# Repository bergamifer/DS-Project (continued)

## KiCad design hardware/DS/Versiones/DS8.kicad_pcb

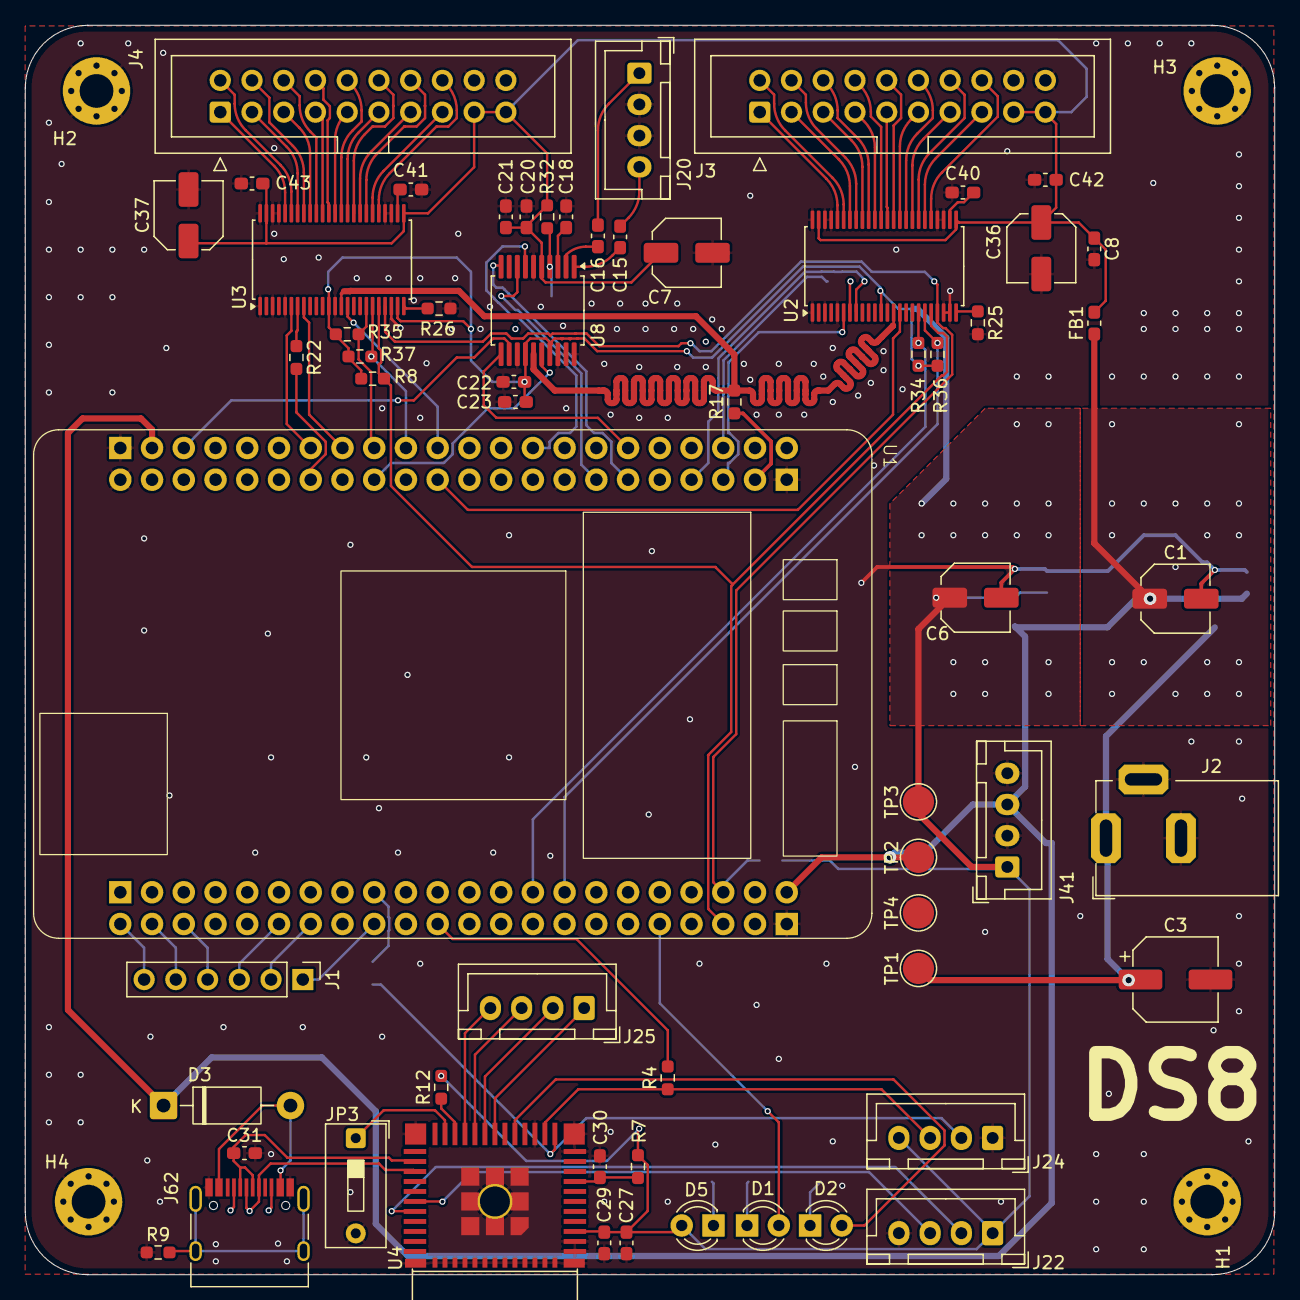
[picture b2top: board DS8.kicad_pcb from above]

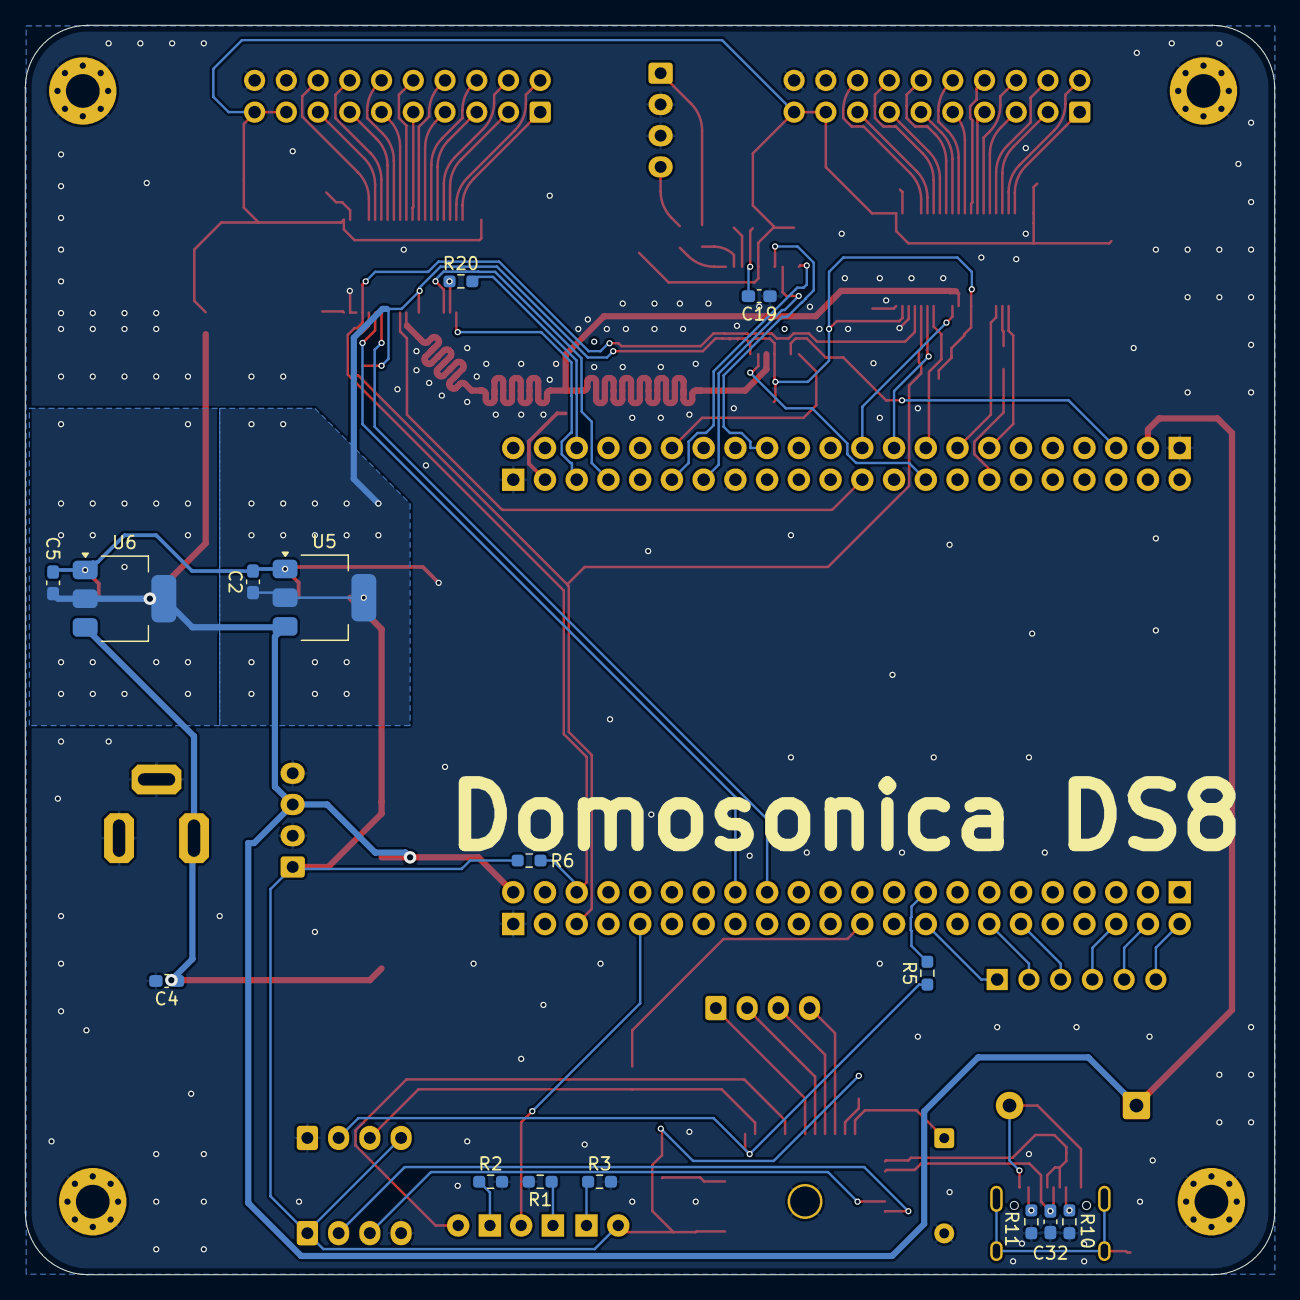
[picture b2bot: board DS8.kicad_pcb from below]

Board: 2 copper layers, 100.0 x 100.0 mm, 80 parts (15 on the bottom side), 101 nets.

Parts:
C1, C6, C7, C36, C37: 10u; C_Elec_5x5.4
C2, C4, C5, C8, C18, C19, C20, C23, C29, C30: 0.1u; C_0603_1608Metric_Pad1.08x0.95mm_HandSolder
C3: 100u; CP_Elec_6.3x5.4
C15, C16, C40, C41, C42, C43: 1u; C_0603_1608Metric_Pad1.08x0.95mm_HandSolder
C21, C22, C27: 10u; C_0603_1608Metric_Pad1.08x0.95mm_HandSolder
C31, C32: 22pF; C_0603_1608Metric_Pad1.08x0.95mm_HandSolder
D1, D2, D5: LED; LED_D3.0mm
D3: 1N5819; D_DO-41_SOD81_P10.16mm_Horizontal
FB1: FerriteBead; L_0603_1608Metric_Pad1.05x0.95mm_HandSolder
H1, H2, H3, H4: MH; MountingHole_2.7mm_Pad_Via
J1: Optional header; PinHeader_1x06_P2.54mm_Vertical
J2: 12v; BarrelJack_CUI_PJ-102AH_Horizontal
J3, J4: Conn_02x10_Odd_Even; IDC-Header_2x10_P2.54mm_Vertical
J20: Audio_IN; JST_XH_B4B-XH-A_1x04_P2.50mm_Vertical
J22: UART0_ESP32; JST_XH_B4B-XH-A_1x04_P2.50mm_Vertical
J24: UART1_ESP32; JST_XH_B4B-XH-A_1x04_P2.50mm_Vertical
J25: JTAG; JST_XH_B4B-XH-A_1x04_P2.50mm_Vertical
J41: Opt_Vout; JST_XH_B4B-XH-A_1x04_P2.50mm_Vertical
J62: USB_C_Receptacle_USB2.0_16P; USB_C_Receptacle_HRO_TYPE-C-31-M-12
JP3: BOOT_ESP32; SW_DIP_SPSTx01_Slide_9.78x4.72mm_W7.62mm_P2.54mm
R1, R3, R25, R26, R32, R34, R35, R36, R37: 1k; R_0603_1608Metric_Pad0.98x0.95mm_HandSolder
R2, R4, R5: 220; R_0603_1608Metric_Pad0.98x0.95mm_HandSolder
R6, R8, R10, R11: 5.1k; R_0603_1608Metric_Pad0.98x0.95mm_HandSolder
R7, R12: 10k; R_0603_1608Metric_Pad0.98x0.95mm_HandSolder
R9: 1M; R_0603_1608Metric_Pad0.98x0.95mm_HandSolder
R17, R20, R22: 33; R_0603_1608Metric_Pad0.98x0.95mm_HandSolder
TP1: +12; TestPoint_Pad_D2.5mm
TP2: +5; TestPoint_Pad_D2.5mm
TP3: +3.3; TestPoint_Pad_D2.5mm
TP4: GND; TestPoint_Pad_D2.5mm
U1: MiniSTM32H7xx
U2, U3: PCM1690; TSSOP-48_6.1x12.5mm_P0.5mm
U4: ESP32-C3-MINI-1; ESP32-C3-MINI-1_HandSoldering
U5: AP1117-33; SOT-223-3_TabPin2
U6: AP1117-50; SOT-223-3_TabPin2
U8: PCM1802; SSOP-20_5.3x7.2mm_P0.65mm

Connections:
+3V3: C2.1, C6.1, C22.2, C23.2, C27.2, C29.1, D5.2 (A), J22.1, J24.4, J41.1, R6.1, R7.2, R8.1, R12.2, R34.1, R35.1, R36.1, R37.1, TP3.1, U2.12 (VDD), U3.12 (VDD), U3.23 (TEST/ADR1/RSV), U4.3 (3V3), U5.2 (VO), U8.14 (VDD), U8.17 (FMT0)
+5V: C1.1, C5.1, D3.1 (K), FB1.1, J41.3, TP2.1, U1.A2 (5V), U1.B42 (5V), U5.3 (VI), U6.2 (VO)
+5VA: C7.1, C8.1, C20.2, C21.2, C36.1, C37.1, C42.1, C43.1, FB1.2, J3.17, J3.19, J4.17, J4.19, R32.2, U2.25 (VCC1), U2.47 (VCC2), U3.25 (VCC1), U3.47 (VCC2), U8.5 (VCC)
+12V: C3.1, C4.1, J2.1, TP1.1, U6.3 (VI)
/ADC/BYPASS: U1.B14 (PC3), U8.8 (BYPAS)
/ADC/OSR: U1.B27 (PB0), U8.16 (OSR)
/ADC/PDWN: U1.B18 (PA1), U8.7 (PDWN)
/ADC/SAI4_FS_B: U1.B11 (PC0), U8.10 (LRCK)
/ADC/SAI4_SCK_B: U1.B12 (PC1), U8.11 (BCK)
/ADC/SAI4_SD_B: U1.B40 (PB11), U8.12 (DOUT)
/DAC0/AMUTEI: R34.2, U1.A18 (PD1), U2.18 (AMUTEI)
/DAC0/AMUTEO: R36.2, U1.A16 (PD3), U2.19 (AMUTEO)
/DAC0/RST: U1.B23 (PA6), U2.15 (RST)
/DAC0/SAI_FS: U1.B5 (PE4), U2.6 (LRCK)
/DAC0/SAI_SCK: R20.2, U1.B6 (PE5)
/DAC0/SAI_SD: U1.B7 (PE6), U2.8 (DIN1)
/DAC0/V1: J3.1, U2.44 (VOUT1-)
/DAC0/V2: J3.2, U2.43 (VOUT1+)
/DAC0/V3: J3.3, U2.42 (VOUT2-)
/DAC0/V4: J3.4, U2.41 (VOUT2+)
/DAC0/V5: J3.5, U2.40 (VOUT3-)
/DAC0/V6: J3.6, U2.39 (VOUT3+)
/DAC0/V7: J3.7, U2.38 (VOUT4-)
/DAC0/V8: J3.8, U2.37 (VOUT4+)
/DAC0/V9: J3.9, U2.36 (VOUT5-)
/DAC0/V10: J3.10, U2.35 (VOUT5+)
/DAC0/V11: J3.11, U2.34 (VOUT6-)
/DAC0/V12: J3.12, U2.33 (VOUT6+)
/DAC0/V13: J3.13, U2.32 (VOUT7-)
/DAC0/V14: J3.14, U2.31 (VOUT7+)
/DAC0/V15: J3.15, U2.30 (VOUT8-)
/DAC0/V16: J3.16, U2.29 (VOUT8+)
/DAC1/AMUTEI: R35.2, U1.B28 (PB1), U3.18 (AMUTEI)
/DAC1/AMUTEO: R37.2, U1.B26 (PC5), U3.19 (AMUTEO)
/DAC1/RST: U1.B24 (PA7), U3.15 (RST)
/DAC1/SAI_FS: U1.B32 (PE9), U3.6 (LRCK)
/DAC1/SAI_SCK: R22.2, U1.B31 (PE8)
/DAC1/SAI_SD: U1.B30 (PE7), U3.8 (DIN1)
/DAC1/V1: J4.1, U3.44 (VOUT1-)
/DAC1/V2: J4.2, U3.43 (VOUT1+)
/DAC1/V3: J4.3, U3.42 (VOUT2-)
/DAC1/V4: J4.4, U3.41 (VOUT2+)
/DAC1/V5: J4.5, U3.40 (VOUT3-)
/DAC1/V6: J4.6, U3.39 (VOUT3+)
/DAC1/V7: J4.7, U3.38 (VOUT4-)
/DAC1/V8: J4.8, U3.37 (VOUT4+)
/DAC1/V9: J4.9, U3.36 (VOUT5-)
/DAC1/V10: J4.10, U3.35 (VOUT5+)
/DAC1/V11: J4.11, U3.34 (VOUT6-)
/DAC1/V12: J4.12, U3.33 (VOUT6+)
/DAC1/V13: J4.13, U3.32 (VOUT7-)
/DAC1/V14: J4.14, U3.31 (VOUT7+)
/DAC1/V15: J4.15, U3.30 (VOUT8-)
/DAC1/V16: J4.16, U3.29 (VOUT8+)
/WeAct miniSTM32/UART7 RX: R5.2, U1.A28 (PA8)
/WeAct miniSTM32/UART7 TX: R4.2, U1.A23 (PA15)
/esp32-mini/UART1 - RX: J24.3, R4.1, U4.13 (GPIO1/ADC1_CH1/XTAL_32K_N)
/esp32-mini/UART1 - TX: J24.2, R5.1, U4.12 (GPIO0/ADC1_CH0/XTAL_32K_P)
GNDA: C1.2, C2.2, C3.2, C4.2, C5.2, C6.2, C7.2, C8.2, C18.1, C19.1, C20.1, C21.1, C22.1, C23.1, C27.1, C29.2, C30.2, C31.2, C32.2, C36.2, C37.2, C40.2, C41.2, C42.2, C43.2, H1.1, H2.1, H3.1, H4.1, J2.2, J2.3, J3.18, J3.20, J4.18, J4.20, J20.2, J20.3, J22.4, J24.1, J41.2, J41.4, J62.A1 (GND), J62.A12 (GND), J62.B1 (GND), J62.B12 (GND), JP3.2 (B), R1.2, R2.2, R3.2, R9.1, R10.1, R11.1, R25.2, R26.2, TP4.1, U1.A1 (GND), U1.B1 (GND), U1.B15 (GND), U1.B43 (GND), U1.B44 (GND), U2.1 (RSV2), U2.3 (RSV2), U2.5 (RSV2), U2.13 (DGND), U2.22 (MS/ADR0/RSV), U2.23 (TEST/ADR1/RSV), U2.27 (AGND1), U2.28 (RSV2), U2.45 (RSV2), U2.46 (AGND2), U2.48 (RSV2), U3.1 (RSV2), U3.3 (RSV2), U3.5 (RSV2), U3.13 (DGND), U3.22 (MS/ADR0/RSV), U3.27 (AGND1), U3.28 (RSV2), U3.45 (RSV2), U3.46 (AGND2), U3.48 (RSV2), U4.1 (GND), U4.2 (GND), U4.11 (GND), U4.14 (GND), U4.36 (GND), U4.37 (GND), U4.38 (GND), U4.39 (GND), U4.40 (GND), U4.41 (GND), U4.42 (GND), U4.43 (GND), U4.44 (GND), U4.45 (GND), U4.46 (GND), U4.47 (GND), U4.48 (GND), U4.49 (GND), U4.50 (GND), U4.51 (GND), U4.52 (GND), U4.53 (GND), U5.1 (GND), U6.1 (GND), U8.6 (AGND), U8.13 (DGND), U8.18 (FMT1), U8.19 (MODE0), U8.20 (MODE1)
I2C_SCL: R6.2, U1.A6 (PB8), U2.21 (MC/SCL/FMT), U3.21 (MC/SCL/FMT)
I2C_SDA: R8.2, U1.A5 (PB9), U2.20 (MD/SDA/DEMP), U3.20 (MD/SDA/DEMP)
LED_STATUS: D1.2 (A), U1.A9 (PB5)
unnamed: D1.1 (K), R1.1
unnamed: D2.2 (A), U4.16 (GPIO10)
unnamed: D2.1 (K), R2.1
unnamed: D3.2 (A), J62.A4 (VBUS), J62.A9 (VBUS), J62.B4 (VBUS), J62.B9 (VBUS)
unnamed: D5.1 (K), R3.1
unnamed: J1.1, U1.A27 (PA9)
unnamed: J1.2, U1.A31 (PC7)
unnamed: J1.3, U1.A33 (PD15)
unnamed: J1.4, U1.A39 (PD9)
unnamed: J1.5, U1.A41 (PB15)
unnamed: J1.6, U1.A43 (PB13)
unnamed: C16.2, J20.1
unnamed: C15.2, J20.4
unnamed: J22.2, U4.31 (GPIO21/U0TXD)
unnamed: J22.3, U4.30 (GPIO20/U0RXD)
unnamed: J25.1, U4.18 (GPIO4/ADC1_CH4)
unnamed: J25.2, U4.19 (GPIO5/ADC2_CH0)
unnamed: J25.3, U4.20 (GPIO6)
unnamed: J25.4, U4.21 (GPIO7)
unnamed: J62.A5 (CC1), R10.2
unnamed: J62.B5 (CC2), R11.2
unnamed: J62.S1 (SHIELD), R9.2
unnamed: JP3.1 (A), U4.23 (GPIO9)
unnamed: R20.1, U2.7 (BCK)
unnamed: R25.1, U2.24 (MODE)
unnamed: C40.1, U2.26 (VCOM)
unnamed: R22.1, U3.7 (BCK)
unnamed: R26.1, U3.24 (MODE)
unnamed: C41.1, U3.26 (VCOM)
unnamed: C30.1, R7.1, U4.8 (EN/CHIP_PU)
unnamed: R12.1, U4.22 (GPIO8)
unnamed: C31.1, J62.A7 (D-), J62.B7 (D-), U4.26 (GPIO18/USB_D-)
unnamed: C32.1, J62.A6 (D+), J62.B6 (D+), U4.27 (GPIO19/USB_D+)
unnamed: C15.1, U8.1 (VINL)
unnamed: C16.1, U8.2 (VINR)
unnamed: C18.2, U8.3 (VREF1)
unnamed: C19.2, R32.1, U8.4 (VREF2)
PE2: R17.1, U1.B3 (PE2)
SAI1_MCLK: R17.2, U2.14 (SCKI), U3.14 (SCKI), U8.15 (SCKI)

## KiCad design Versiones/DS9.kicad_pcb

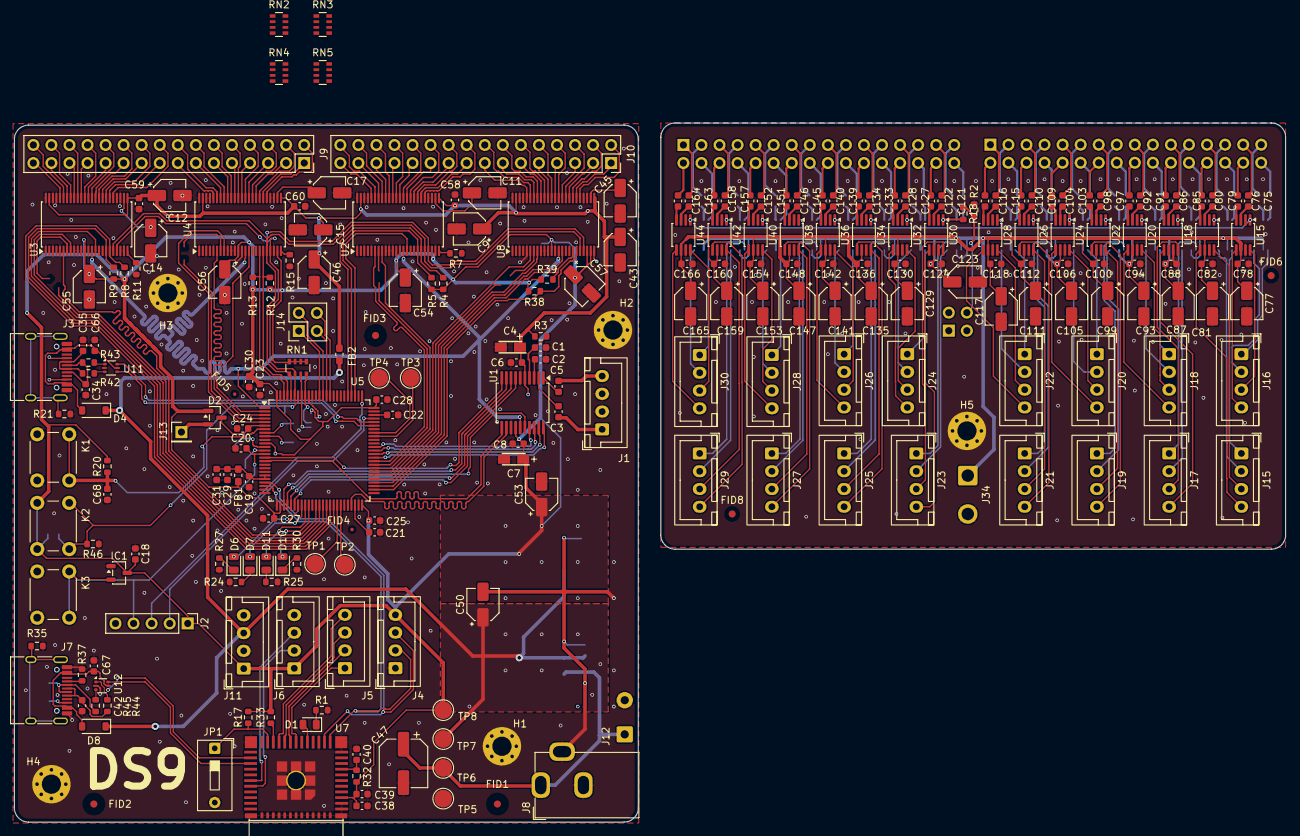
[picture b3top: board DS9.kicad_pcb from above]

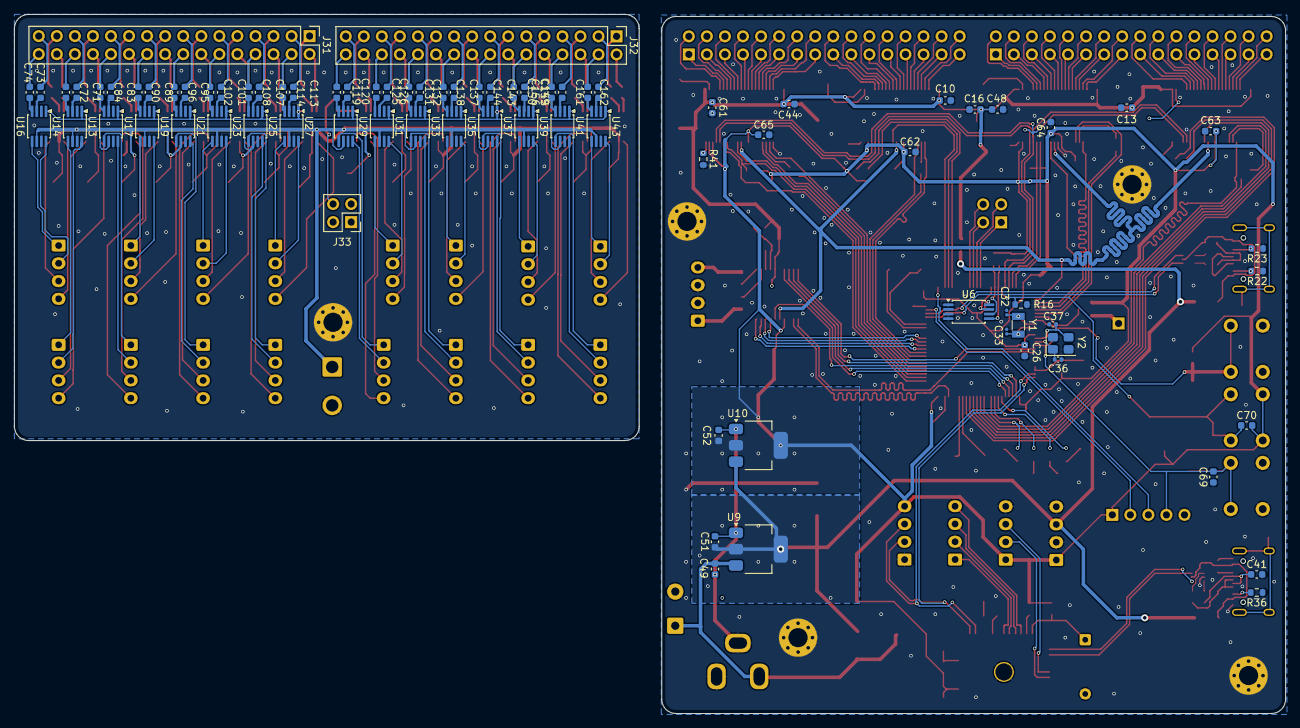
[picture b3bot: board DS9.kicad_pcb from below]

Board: 2 copper layers, 178.8 x 98.3 mm, 322 parts (82 on the bottom side), 399 nets.

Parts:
C1, C2, C6, C8, C18, C20, C24, C25, C26, C27, C28, C29, C30, C39, C40, C48, C49, C51, C52, C68, C69, C70, C71, C72, C73, C74, C75, C76, C79, C80, C83, C84, C85, C86, C89, C90, C91, C92, C95, C96, C97, C98, C101, C102, C103, C104, C107, C108, C109, C110, C113, C114, C115, C116, C119, C120, C121, C122, C125, C126, C127, C128, C131, C132, C133, C134, C137, C138, C139, C140, C143, C144, C145, C146, C149, C150, C151, C152, C155, C156, C157, C158, C161, C162, C163, C164: 0.1u; C_0603_1608Metric
C3, C5, C10, C13, C16, C19, C44, C58, C59, C60, C61, C62, C63, C64, C65, C78, C82, C88, C94, C100, C106, C112, C118, C124, C130, C136, C142, C148, C154, C160, C166: 1u; C_0603_1608Metric
C4, C7: 10u TANT; CAPPM3216X180N
C9, C11, C12, C14, C15, C17, C43, C45, C46, C50, C53, C54, C55, C56, C57, C77, C81, C87, C93, C99, C105, C111, C117, C123, C129, C135, C141, C147, C153, C159, C165: 10u EL; CP_Elec_4x5.7
C21, C22: 2.2u; C_0603_1608Metric
C23, C66, C67: 4.7u; C_0603_1608Metric
C31, C38: 10u cer; C_0603_1608Metric
C32, C33: 8.2pF; C_0201_0603Metric
C34, C35, C41, C42: 22p; C_0603_1608Metric
C36, C37: 18pF; C_0402_1005Metric
C47: 100u; CP_Elec_6.3x7.7
D1, D7: Red LED; LED_0805_2012Metric
D2: BAT54C; SOT-23
D4, D8: B5819W SL; D_SOD-123
D6: Yellow LED; LED_0805_2012Metric
D10: White LED; LED_0805_2012Metric
D11: Green LED; LED_0805_2012Metric
FB1, FB2: FerriteBead; L_0603_1608Metric_Pad1.05x0.95mm_HandSolder
FID1, FID2, FID3: Fiducial; Fiducial_1mm_Mask3mm
FID4, FID5: Fiducial; Fiducial_0.5mm_Mask1mm
FID6, FID8: Fiducial; Fiducial_1mm_Mask2mm
H1, H2, H3, H4, H5: MH; MountingHole_2.7mm_Pad_Via
IC1: MAX809TEUR+T; SOT-23-3
J1: Audio_IN; JST_XH_B4B-XH-A_1x04_P2.50mm_Vertical
J2: STM_Debug; PinHeader_1x05_P2.54mm_Vertical
J3, J7: USB_C; USB_C_Receptacle_HRO_TYPE-C-31-M-12
J4: UART1_ESP32; JST_XH_B4B-XH-A_1x04_P2.50mm_Vertical
J5: JTAG; JST_XH_B4B-XH-A_1x04_P2.50mm_Vertical
J6: UART0_ESP32; JST_XH_B4B-XH-A_1x04_P2.50mm_Vertical
J8: 12v; BarrelJack_CUI_PJ-102AH_Horizontal
J9, J10: Conn_02x16; PinSocket_2x16_P2.54mm_Vertical
J11: Opt_Vout; JST_XH_B4B-XH-A_1x04_P2.50mm_Vertical
J12: Conn_01x02; SolderWire-0.5sqmm_1x02_P4.8mm_D0.9mm_OD2.3mm
J13: VBat; PinHeader_1x01_P2.54mm_Vertical
J14: Extra_pins; PinHeader_2x02_P2.54mm_Vertical
J15, J16, J17, J18, J19, J20, J21, J22, J23, J24, J25, J26, J27, J28, J29, J30: SPK_OUT; JST_XH_B4B-XH-A_1x04_P2.50mm_Vertical
J31, J32: Conn_02x16; PinHeader_2x16_P2.54mm_Vertical
J33: Extra_pins; PinSocket_2x02_P2.54mm_Vertical
J34: Conn_01x02; SolderWire-1sqmm_1x02_P5.4mm_D1.4mm_OD2.7mm
JP1: BOOT_ESP32; SW_DIP_SPSTx01_Slide_9.78x4.72mm_W7.62mm_P2.54mm
K1, K2, K3: SW_Push; SW_PUSH_6mm
R1, R24: 150; R_0603_1608Metric
R2, R3, R4, R5, R7, R8, R9, R11, R12, R13, R15, R38, R39, R41: 1k; R_0603_1608Metric
R16, R17, R20, R32, R33, R46: 10k; R_0603_1608Metric
R18, R42, R43, R44, R45: 33; R_0603_1608Metric
R21, R35: 1M; R_0603_1608Metric
R22, R23, R36, R37: 5.1k; R_0603_1608Metric
R25: 100; R_0603_1608Metric
R27: 200; R_0603_1608Metric
R30: 82; R_0603_1608Metric
RN1: 4.7k; R_Array_Convex_4x0603
RN2, RN3, RN4, RN5: 33; R_Array_Convex_4x0603
TP1: TP_SAI1_FS; TestPoint_Pad_D2.5mm
TP2: TP_SAI_DEBUG; TestPoint_Pad_D2.5mm
TP3: TP_DEBUG; TestPoint_Pad_D2.5mm
TP4: TP_DEBUG2; TestPoint_Pad_D2.5mm
TP5: +12; TestPoint_Pad_D2.5mm
TP6: +5; TestPoint_Pad_D2.5mm
TP7: +3.3; TestPoint_Pad_D2.5mm
TP8: GND; TestPoint_Pad_D2.5mm
U1: PCM1802; SSOP-20_5.3x7.2mm_P0.65mm
U2, U3, U4, U8: PCM1690; TSSOP-48_6.1x12.5mm_P0.5mm
U5: STM32H743VITx; LQFP-100_14x14mm_P0.5mm
U6: CAT24C256; TSSOP-8_4.4x3mm_P0.65mm
U7: ESP32-C3-MINI-1; ESP32-C3-MINI-1_HandSoldering
U9: AP1117-50; SOT-223-3_TabPin2
U10: AP1117-33; SOT-223-3_TabPin2
U11, U12: USBLC6-2P6; SOT-666
U13, U14, U15, U16, U17, U18, U19, U20, U21, U22, U23, U24, U25, U26, U27, U28, U29, U30, U31, U32, U33, U34, U35, U36, U37, U38, U39, U40, U41, U42, U43, U44: PAM8302; MSOP-8_3x3mm_P0.65mm
Y1: 32.768K 7pF; Crystal_SMD_3215-2Pin_3.2x1.5mm
Y2: 25MHz 12pF; Crystal_SMD_3225-4Pin_3.2x2.5mm

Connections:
+3V3: C7.1, C8.2, C18.2, C23.1, C25.1, C26.1, C27.1, C28.1, C30.1, C38.2, C39.1, C52.1, C53.1, C54.1, C55.1, C56.1, C57.1, C62.1, C63.1, C64.1, C65.1, C70.2, D2.1, FB1.2, IC1.3 (VCC), J2.1, J4.4, J6.1, J11.1, K2.1, R4.1, R5.1, R8.1, R9.1, R12.1, R13.1, R17.2, R20.2, R32.2, R33.2, R38.1, R39.1, RN1.5 (R4.2), RN1.6 (R3.2), RN1.7 (R2.2), RN1.8 (R1.2), TP8.1, U1.14 (VDD), U2.12 (VDD), U2.22 (MS/ADR0/RSV), U3.12 (VDD), U4.12 (VDD), U4.23 (TEST/ADR1/RSV), U5.11 (VDD), U5.27 (VDD), U5.50 (VDD), U5.75 (VDD), U5.100 (VDD), U6.8 (VCC), U7.3 (3V3), U8.12 (VDD), U8.22 (MS/ADR0/RSV), U8.23 (TEST/ADR1/RSV), U10.2 (VO)
+5V: C50.1, C51.1, D4.1 (K), D8.1 (K), FB2.1, J11.3, TP7.1, U9.2 (VO), U10.3 (VI)
+5VA: C4.1, C6.2, C9.1, C10.1, C12.1, C13.1, C15.1, C16.1, C43.1, C44.1, C46.1, C48.1, C58.1, C59.1, C60.1, C61.1, FB2.2, R3.2, U1.5 (VCC), U2.25 (VCC1), U2.47 (VCC2), U3.25 (VCC1), U3.47 (VCC2), U4.25 (VCC1), U4.47 (VCC2), U8.25 (VCC1), U8.47 (VCC2)
+12V: C47.1, C49.1, J8.1, J12.1, TP6.1, U9.3 (VI)
/ADC/BYPASS: U1.8 (BYPAS), U5.30 (PA6)
/ADC/FMT0: U1.17 (FMT0), U5.64 (PC7)
/ADC/FMT1: U1.18 (FMT1), U5.63 (PC6)
/ADC/Frame Sync: U1.9 (FSYNC), U5.28 (PA4)
/ADC/MODE0: U1.19 (MODE0), U5.62 (PD15)
/ADC/MODE1: U1.20 (MODE1), U5.61 (PD14)
/ADC/OSR: U1.16 (OSR), U5.29 (PA5)
/ADC/PDWN: U1.7 (PDWN), U5.31 (PA7)
/ADC/SAI4_FS_B: U1.10 (LRCK), U5.15 (PC0)
/ADC/SAI4_SCK_B: U1.11 (BCK), U5.16 (PC1)
/ADC/SAI4_SD_B: U1.12 (DOUT), U5.47 (PB11)
/DAC0/AMUTEI: R9.2, U3.18 (AMUTEI), U5.41 (PE11)
/DAC0/AMUTEO: R8.2, U3.19 (AMUTEO), U5.42 (PE12)
/DAC0/RST: U3.15 (RST), U5.40 (PE10)
/DAC0/SAI_FS: RN3.1 (R1.1), U5.37 (PE7)
/DAC0/SAI_SCK: RN3.2 (R2.1), U5.38 (PE8)
/DAC0/SAI_SD: RN3.3 (R3.1), U5.39 (PE9)
/DAC0/V1: J9.31, U3.44 (VOUT1-)
/DAC0/V2: J9.32, U3.43 (VOUT1+)
/DAC0/V3: J9.29, U3.42 (VOUT2-)
/DAC0/V4: J9.30, U3.41 (VOUT2+)
/DAC0/V5: J9.27, U3.40 (VOUT3-)
/DAC0/V6: J9.28, U3.39 (VOUT3+)
/DAC0/V7: J9.25, U3.38 (VOUT4-)
/DAC0/V8: J9.26, U3.37 (VOUT4+)
/DAC0/V9: J9.23, U3.36 (VOUT5-)
/DAC0/V10: J9.24, U3.35 (VOUT5+)
/DAC0/V11: J9.21, U3.34 (VOUT6-)
/DAC0/V12: J9.22, U3.33 (VOUT6+)
/DAC0/V13: J9.19, U3.32 (VOUT7-)
/DAC0/V14: J9.20, U3.31 (VOUT7+)
/DAC0/V15: J9.17, U3.30 (VOUT8-)
/DAC0/V16: J9.18, U3.29 (VOUT8+)
/DAC1/AMUTEI: R13.2, U4.18 (AMUTEI), U5.98 (PE1)
/DAC1/AMUTEO: R12.2, U4.19 (AMUTEO), U5.97 (PE0)
/DAC1/RST: U4.15 (RST), U5.2 (PE3)
/DAC1/SAI_FS: RN4.1 (R1.1), U5.3 (PE4)
/DAC1/SAI_SCK: RN4.2 (R2.1), U5.4 (PE5)
/DAC1/SAI_SD: RN4.3 (R3.1), U5.5 (PE6)
/DAC1/V1: J9.15, U4.44 (VOUT1-)
/DAC1/V2: J9.16, U4.43 (VOUT1+)
/DAC1/V3: J9.13, U4.42 (VOUT2-)
/DAC1/V4: J9.14, U4.41 (VOUT2+)
/DAC1/V5: J9.11, U4.40 (VOUT3-)
/DAC1/V6: J9.12, U4.39 (VOUT3+)
/DAC1/V7: J9.9, U4.38 (VOUT4-)
/DAC1/V8: J9.10, U4.37 (VOUT4+)
/DAC1/V9: J9.7, U4.36 (VOUT5-)
/DAC1/V10: J9.8, U4.35 (VOUT5+)
/DAC1/V11: J9.5, U4.34 (VOUT6-)
/DAC1/V12: J9.6, U4.33 (VOUT6+)
/DAC1/V13: J9.3, U4.32 (VOUT7-)
/DAC1/V14: J9.4, U4.31 (VOUT7+)
/DAC1/V15: J9.1, U4.30 (VOUT8-)
/DAC1/V16: J9.2, U4.29 (VOUT8+)
/DAC2/AMUTEI: R5.2, U2.18 (AMUTEI), U5.79 (PC11)
/DAC2/AMUTEO: R4.2, U2.19 (AMUTEO), U5.80 (PC12)
/DAC2/RST: U2.15 (RST), U5.78 (PC10)
/DAC2/SAI_FS: RN2.1 (R1.1), U5.60 (PD13)
/DAC2/SAI_SCK: RN2.2 (R2.1), U5.59 (PD12)
/DAC2/SAI_SD: RN2.3 (R3.1), U5.58 (PD11)
/DAC2/V1: J10.31, U2.44 (VOUT1-)
/DAC2/V2: J10.32, U2.43 (VOUT1+)
/DAC2/V3: J10.29, U2.42 (VOUT2-)
/DAC2/V4: J10.30, U2.41 (VOUT2+)
/DAC2/V5: J10.27, U2.40 (VOUT3-)
/DAC2/V6: J10.28, U2.39 (VOUT3+)
/DAC2/V7: J10.25, U2.38 (VOUT4-)
/DAC2/V8: J10.26, U2.37 (VOUT4+)
/DAC2/V9: J10.23, U2.36 (VOUT5-)
/DAC2/V10: J10.24, U2.35 (VOUT5+)
/DAC2/V11: J10.21, U2.34 (VOUT6-)
/DAC2/V12: J10.22, U2.33 (VOUT6+)
/DAC2/V13: J10.19, U2.32 (VOUT7-)
/DAC2/V14: J10.20, U2.31 (VOUT7+)
/DAC2/V15: J10.17, U2.30 (VOUT8-)
/DAC2/V16: J10.18, U2.29 (VOUT8+)
/DAC3/AMUTEI: R39.2, U5.53 (PB14), U8.18 (AMUTEI)
/DAC3/AMUTEO: R38.2, U5.52 (PB13), U8.19 (AMUTEO)
/DAC3/RST: U5.54 (PB15), U8.15 (RST)
/DAC3/SAI_FS: RN5.1 (R1.1), U5.57 (PD10)
/DAC3/SAI_SCK: RN5.2 (R2.1), U5.56 (PD9)
/DAC3/SAI_SD: RN5.3 (R3.1), U5.55 (PD8)
/DAC3/V1: J10.15, U8.44 (VOUT1-)
/DAC3/V2: J10.16, U8.43 (VOUT1+)
/DAC3/V3: J10.13, U8.42 (VOUT2-)
/DAC3/V4: J10.14, U8.41 (VOUT2+)
/DAC3/V5: J10.11, U8.40 (VOUT3-)
/DAC3/V6: J10.12, U8.39 (VOUT3+)
/DAC3/V7: J10.9, U8.38 (VOUT4-)
/DAC3/V8: J10.10, U8.37 (VOUT4+)
/DAC3/V9: J10.7, U8.36 (VOUT5-)
/DAC3/V10: J10.8, U8.35 (VOUT5+)
/DAC3/V11: J10.5, U8.34 (VOUT6-)
/DAC3/V12: J10.6, U8.33 (VOUT6+)
/DAC3/V13: J10.3, U8.32 (VOUT7-)
/DAC3/V14: J10.4, U8.31 (VOUT7+)
/DAC3/V15: J10.1, U8.30 (VOUT8-)
/DAC3/V16: J10.2, U8.29 (VOUT8+)
/HAT_Amplifiers/ALL_AMPS/AMP1: C73.2, J31.31
/HAT_Amplifiers/ALL_AMPS/AMP2: C74.1, J31.32
/HAT_Amplifiers/ALL_AMPS/AMP3: C75.2, J31.29
/HAT_Amplifiers/ALL_AMPS/AMP4: C76.1, J31.30
/HAT_Amplifiers/ALL_AMPS/AMP5: C71.2, J31.27
/HAT_Amplifiers/ALL_AMPS/AMP6: C72.1, J31.28
/HAT_Amplifiers/ALL_AMPS/AMP7: C79.2, J31.25
/HAT_Amplifiers/ALL_AMPS/AMP8: C80.1, J31.26
/HAT_Amplifiers/ALL_AMPS/AMP9: C83.2, J31.23
/HAT_Amplifiers/ALL_AMPS/AMP10: C84.1, J31.24
/HAT_Amplifiers/ALL_AMPS/AMP11: C85.2, J31.21
/HAT_Amplifiers/ALL_AMPS/AMP12: C86.1, J31.22
/HAT_Amplifiers/ALL_AMPS/AMP13: C89.2, J31.19
/HAT_Amplifiers/ALL_AMPS/AMP14: C90.1, J31.20
/HAT_Amplifiers/ALL_AMPS/AMP15: C91.2, J31.17
/HAT_Amplifiers/ALL_AMPS/AMP16: C92.1, J31.18
/HAT_Amplifiers/ALL_AMPS/AMP17: C95.2, J31.15
/HAT_Amplifiers/ALL_AMPS/AMP18: C96.1, J31.16
/HAT_Amplifiers/ALL_AMPS/AMP19: C97.2, J31.13
/HAT_Amplifiers/ALL_AMPS/AMP20: C98.1, J31.14
/HAT_Amplifiers/ALL_AMPS/AMP21: C101.2, J31.11
/HAT_Amplifiers/ALL_AMPS/AMP22: C102.1, J31.12
/HAT_Amplifiers/ALL_AMPS/AMP23: C103.2, J31.9
/HAT_Amplifiers/ALL_AMPS/AMP24: C104.1, J31.10
/HAT_Amplifiers/ALL_AMPS/AMP25: C107.2, J31.7
/HAT_Amplifiers/ALL_AMPS/AMP26: C108.1, J31.8
/HAT_Amplifiers/ALL_AMPS/AMP27: C109.2, J31.5
/HAT_Amplifiers/ALL_AMPS/AMP28: C110.1, J31.6
/HAT_Amplifiers/ALL_AMPS/AMP29: C113.2, J31.3
/HAT_Amplifiers/ALL_AMPS/AMP30: C114.1, J31.4
/HAT_Amplifiers/ALL_AMPS/AMP31: C115.2, J31.1
/HAT_Amplifiers/ALL_AMPS/AMP32: C116.1, J31.2
/HAT_Amplifiers/ALL_AMPS/AMP33: C119.2, J32.31
/HAT_Amplifiers/ALL_AMPS/AMP34: C120.1, J32.32
/HAT_Amplifiers/ALL_AMPS/AMP35: C121.2, J32.29
/HAT_Amplifiers/ALL_AMPS/AMP36: C122.1, J32.30
/HAT_Amplifiers/ALL_AMPS/AMP37: C125.2, J32.27
/HAT_Amplifiers/ALL_AMPS/AMP38: C126.1, J32.28
/HAT_Amplifiers/ALL_AMPS/AMP39: C127.2, J32.25
/HAT_Amplifiers/ALL_AMPS/AMP40: C128.1, J32.26
/HAT_Amplifiers/ALL_AMPS/AMP41: C131.2, J32.23
/HAT_Amplifiers/ALL_AMPS/AMP42: C132.1, J32.24
/HAT_Amplifiers/ALL_AMPS/AMP43: C133.2, J32.21
/HAT_Amplifiers/ALL_AMPS/AMP44: C134.1, J32.22
/HAT_Amplifiers/ALL_AMPS/AMP45: C137.2, J32.19
/HAT_Amplifiers/ALL_AMPS/AMP46: C138.1, J32.20
/HAT_Amplifiers/ALL_AMPS/AMP47: C139.2, J32.17
/HAT_Amplifiers/ALL_AMPS/AMP48: C140.1, J32.18
/HAT_Amplifiers/ALL_AMPS/AMP49: C143.2, J32.15
/HAT_Amplifiers/ALL_AMPS/AMP50: C144.1, J32.16
/HAT_Amplifiers/ALL_AMPS/AMP51: C145.2, J32.13
/HAT_Amplifiers/ALL_AMPS/AMP52: C146.1, J32.14
/HAT_Amplifiers/ALL_AMPS/AMP53: C149.2, J32.11
/HAT_Amplifiers/ALL_AMPS/AMP54: C150.1, J32.12
/HAT_Amplifiers/ALL_AMPS/AMP55: C151.2, J32.9
/HAT_Amplifiers/ALL_AMPS/AMP56: C152.1, J32.10
/HAT_Amplifiers/ALL_AMPS/AMP57: C155.2, J32.7
/HAT_Amplifiers/ALL_AMPS/AMP58: C156.1, J32.8
/HAT_Amplifiers/ALL_AMPS/AMP59: C157.2, J32.5
/HAT_Amplifiers/ALL_AMPS/AMP60: C158.1, J32.6
/HAT_Amplifiers/ALL_AMPS/AMP61: C161.2, J32.3
/HAT_Amplifiers/ALL_AMPS/AMP62: C162.1, J32.4
/HAT_Amplifiers/ALL_AMPS/AMP63: C163.2, J32.1
/HAT_Amplifiers/ALL_AMPS/AMP64: C164.1, J32.2
/HAT_Amplifiers/ALL_AMPS/SD: R18.2, U13.1 (~SD), U14.1 (~SD), U15.1 (~SD), U16.1 (~SD), U17.1 (~SD), U18.1 (~SD), U19.1 (~SD), U20.1 (~SD), U21.1 (~SD), U22.1 (~SD), U23.1 (~SD), U24.1 (~SD), U25.1 (~SD), U26.1 (~SD), U27.1 (~SD), U28.1 (~SD), U29.1 (~SD), U30.1 (~SD), U31.1 (~SD), U32.1 (~SD), U33.1 (~SD), U34.1 (~SD), U35.1 (~SD), U36.1 (~SD), U37.1 (~SD), U38.1 (~SD), U39.1 (~SD), U40.1 (~SD), U41.1 (~SD), U42.1 (~SD), U43.1 (~SD), U44.1 (~SD)
/esp32-mini/GPIO18/USB_D-: U7.26 (GPIO18/USB_D-), U12.4 (I/O2)
/esp32-mini/GPIO19/USB_D+: U7.27 (GPIO19/USB_D+), U12.6 (I/O1)
/esp32-mini/UART1 - RX: J4.3, U5.22 (PA0), U7.13 (GPIO1/ADC1_CH1/XTAL_32K_N)
/esp32-mini/UART1 - TX: J4.2, U5.23 (PA1), U7.12 (GPIO0/ADC1_CH0/XTAL_32K_P)
/esp32-mini/VBUS: C67.1, D8.2 (A), J7.A4 (VBUS), J7.A9 (VBUS), J7.B4 (VBUS), J7.B9 (VBUS), U12.5 (VBUS)
/stm32_custom/BOOT0: C70.1, K2.2, R16.1, R46.2, U5.94 (BOOT0)
/stm32_custom/NRST: C20.2, C69.2, IC1.2 (~RESET), J2.4, K3.1, U5.14 (NRST)
/stm32_custom/PA13: J2.2, U5.72 (PA13)
/stm32_custom/PA14: J2.3, U5.76 (PA14)
/stm32_custom/PB0: D11.2 (A), U5.34 (PB0)
/stm32_custom/PB1: D10.2 (A), U5.35 (PB1)
/stm32_custom/PC4: D6.2 (A), U5.32 (PC4)
/stm32_custom/PC5: D7.2 (A), U5.33 (PC5)
/stm32_custom/PD4: J14.4, U5.85 (PD4)
/stm32_custom/PD5: J14.3, U5.86 (PD5)
/stm32_custom/PD6: J14.2, U5.87 (PD6)
/stm32_custom/PD7: J14.1, U5.88 (PD7)
/stm32_custom/PH0: C37.1, U5.12 (PH0), Y2.3
/stm32_custom/PH1: C36.2, U5.13 (PH1), Y2.1
/stm32_custom/VBAT: C24.2, D2.3, U5.6 (VBAT)
/stm32_custom/VBUS: C66.1, D4.2 (A), J3.A4 (VBUS), J3.A9 (VBUS), J3.B4 (VBUS), J3.B9 (VBUS), U11.5 (VBUS)
/stm32_custom/VREF+: C19.1, C29.1, C31.1, FB1.1, U5.20 (VREF+), U5.21 (VDDA)
EEPROM_WP: U5.91 (PB5), U6.7 (WP)
GND2: C77.2, C78.1, C81.2, C82.1, C87.2, C88.1, C93.2, C94.1, C99.2, C100.1, C105.2, C106.1, C111.2, C112.1, C117.2, C118.1, C123.2, C124.1, C129.2, C130.1, C135.2, C136.1, C141.2, C142.1, C147.2, C148.1, C153.2, C154.1, C159.2, C160.1, C165.2, C166.1, H5.1, J34.2, R2.2, U13.7 (GND), U14.7 (GND), U15.7 (GND), U16.7 (GND), U17.7 (GND), U18.7 (GND), U19.7 (GND), U20.7 (GND), U21.7 (GND), U22.7 (GND), U23.7 (GND), U24.7 (GND), U25.7 (GND), U26.7 (GND), U27.7 (GND), U28.7 (GND), U29.7 (GND), U30.7 (GND), U31.7 (GND), U32.7 (GND), U33.7 (GND), U34.7 (GND), U35.7 (GND), U36.7 (GND), U37.7 (GND), U38.7 (GND), U39.7 (GND), U40.7 (GND), U41.7 (GND), U42.7 (GND), U43.7 (GND), U44.7 (GND)
GNDA: C1.1, C2.1, C4.2, C6.1, C7.2, C8.1, C9.2, C10.2, C11.2, C12.2, C13.2, C14.2, C15.2, C16.2, C17.2, C18.1, C19.2, C20.1, C21.2, C22.2, C23.2, C24.1, C25.2, C26.2, C27.2, C28.2, C29.2, C30.2, C31.2, C32.2, C33.2, C34.1, C35.2, C36.1, C37.2, C38.1, C39.2, C40.2, C41.2, C42.2, C43.2, C44.2, C45.2, C46.2, C47.2, C48.2, C49.2, C50.2, C51.2, C52.2, C53.2, C54.2, C55.2, C56.2, C57.2, C58.2, C59.2, C60.2, C61.2, C62.2, C63.2, C64.2, C65.2, C66.2, C67.2, C68.1, C69.1, H1.1, H2.1, H3.1, H4.1, IC1.1 (GND), J1.2, J1.3, J2.5, J3.A1 (GND), J3.A12 (GND), J3.B1 (GND), J3.B12 (GND), J4.1, J6.4, J7.A1 (GND), J7.A12 (GND), J7.B1 (GND), J7.B12 (GND), J8.2, J8.3, J11.2, J11.4, J12.2, JP1.2 (B), K1.2, K3.2, R1.2, R7.2, R11.2, R15.2, R16.2, R21.1, R22.1, R23.1, R24.2, R25.2, R27.2, R30.2, R35.1, R36.1, R37.1, R41.2, R46.1, TP5.1, U1.6 (AGND), U1.13 (DGND), U2.1 (RSV2), U2.3 (RSV2), U2.5 (RSV2), U2.9 (DIN2), U2.10 (DIN3), U2.11 (DIN4), U2.13 (DGND), U2.23 (TEST/ADR1/RSV), U2.27 (AGND1), U2.28 (RSV2), U2.45 (RSV2), U2.46 (AGND2), U2.48 (RSV2), U3.1 (RSV2), U3.3 (RSV2), U3.5 (RSV2), U3.9 (DIN2), U3.10 (DIN3), U3.11 (DIN4), U3.13 (DGND), U3.22 (MS/ADR0/RSV), U3.23 (TEST/ADR1/RSV), U3.27 (AGND1), U3.28 (RSV2), U3.45 (RSV2), U3.46 (AGND2), U3.48 (RSV2), U4.1 (RSV2), U4.3 (RSV2), U4.5 (RSV2), U4.9 (DIN2), U4.10 (DIN3), U4.11 (DIN4), U4.13 (DGND), U4.22 (MS/ADR0/RSV), U4.27 (AGND1), U4.28 (RSV2), U4.45 (RSV2), U4.46 (AGND2), U4.48 (RSV2), U5.10 (VSS), U5.19 (VSSA), U5.26 (VSS), U5.49 (VSS), U5.74 (VSS), U5.99 (VSS), U6.1 (A0), U6.2 (A1), U6.3 (A2), U6.4 (GND), U7.1 (GND), U7.2 (GND), U7.11 (GND), U7.14 (GND), U7.36 (GND), U7.37 (GND), U7.38 (GND), U7.39 (GND), U7.40 (GND), U7.41 (GND), U7.42 (GND), U7.43 (GND), U7.44 (GND), U7.45 (GND), U7.46 (GND), U7.47 (GND), U7.48 (GND), U7.49 (GND), U7.50 (GND), U7.51 (GND), U7.52 (GND), U7.53 (GND), U8.1 (RSV2), U8.3 (RSV2), U8.5 (RSV2), U8.9 (DIN2), U8.10 (DIN3), U8.11 (DIN4), U8.13 (DGND), U8.27 (AGND1), U8.28 (RSV2), U8.45 (RSV2), U8.46 (AGND2), U8.48 (RSV2), U9.1 (GND), U10.1 (GND), U11.2 (GND), U12.2 (GND), Y2.2 (G), Y2.4 (G)
I2C1_SCL: RN1.2 (R2.1), U2.21 (MC/SCL/FMT), U3.21 (MC/SCL/FMT), U4.21 (MC/SCL/FMT), U5.95 (PB8), U8.21 (MC/SCL/FMT)
I2C1_SDA: RN1.1 (R1.1), U2.20 (MD/SDA/DEMP), U3.20 (MD/SDA/DEMP), U4.20 (MD/SDA/DEMP), U5.96 (PB9), U8.20 (MD/SDA/DEMP)
I2C3_SCL: RN1.4 (R4.1), U5.92 (PB6), U6.6 (SCL)
I2C3_SDA: RN1.3 (R3.1), U5.93 (PB7), U6.5 (SDA)
unnamed: C21.1, U5.48 (VCAP)
unnamed: C22.1, U5.73 (VCAP)
unnamed: C34.2, J3.A6 (D+), J3.B6 (D+), R43.2
unnamed: C35.1, J3.A7 (D-), J3.B7 (D-), R42.2
unnamed: C41.1, J7.A7 (D-), J7.B7 (D-), R45.1
unnamed: C42.1, J7.A6 (D+), J7.B6 (D+), R44.1
unnamed: D1.2 (A), U7.16 (GPIO10)
unnamed: D1.1 (K), R1.1
unnamed: D6.1 (K), R27.1
unnamed: D7.1 (K), R24.1
unnamed: D10.1 (K), R30.1
unnamed: D11.1 (K), R25.1
unnamed: C3.2, J1.1
unnamed: C5.2, J1.4
unnamed: J3.A5 (CC1), R23.2
unnamed: J3.B5 (CC2), R22.2
unnamed: J3.S1 (SHIELD), R21.2
unnamed: J5.1, U7.18 (GPIO4/ADC1_CH4)
unnamed: J5.2, U7.19 (GPIO5/ADC2_CH0)
unnamed: J5.3, U7.20 (GPIO6)
unnamed: J5.4, U7.21 (GPIO7)
unnamed: J6.2, U7.31 (GPIO21/U0TXD)
unnamed: J6.3, U7.30 (GPIO20/U0RXD)
unnamed: J7.A5 (CC1), R37.2
unnamed: J7.B5 (CC2), R36.2
unnamed: J7.S1 (SHIELD), R35.2
unnamed: J15.1, U13.5 (OUT+)
unnamed: J15.2, U13.8 (OUT-)
unnamed: J15.3, U16.8 (OUT-)
unnamed: J15.4, U16.5 (OUT+)
unnamed: J16.1, U14.5 (OUT+)
unnamed: J16.2, U14.8 (OUT-)
unnamed: J16.3, U15.8 (OUT-)
unnamed: J16.4, U15.5 (OUT+)
unnamed: J17.1, U17.5 (OUT+)
unnamed: J17.2, U17.8 (OUT-)
unnamed: J17.3, U18.8 (OUT-)
unnamed: J17.4, U18.5 (OUT+)
unnamed: J18.1, U19.5 (OUT+)
unnamed: J18.2, U19.8 (OUT-)
unnamed: J18.3, U20.8 (OUT-)
unnamed: J18.4, U20.5 (OUT+)
unnamed: J19.1, U21.5 (OUT+)
unnamed: J19.2, U21.8 (OUT-)
unnamed: J19.3, U22.8 (OUT-)
unnamed: J19.4, U22.5 (OUT+)
unnamed: J20.1, U23.5 (OUT+)
unnamed: J20.2, U23.8 (OUT-)
unnamed: J20.3, U24.8 (OUT-)
unnamed: J20.4, U24.5 (OUT+)
unnamed: J21.1, U25.5 (OUT+)
unnamed: J21.2, U25.8 (OUT-)
unnamed: J21.3, U26.8 (OUT-)
unnamed: J21.4, U26.5 (OUT+)
unnamed: J22.1, U27.5 (OUT+)
unnamed: J22.2, U27.8 (OUT-)
unnamed: J22.3, U28.8 (OUT-)
unnamed: J22.4, U28.5 (OUT+)
unnamed: J23.1, U29.5 (OUT+)
unnamed: J23.2, U29.8 (OUT-)
unnamed: J23.3, U30.8 (OUT-)
unnamed: J23.4, U30.5 (OUT+)
unnamed: J24.1, U31.5 (OUT+)
unnamed: J24.2, U31.8 (OUT-)
unnamed: J24.3, U32.8 (OUT-)
unnamed: J24.4, U32.5 (OUT+)
unnamed: J25.1, U33.5 (OUT+)
unnamed: J25.2, U33.8 (OUT-)
unnamed: J25.3, U34.8 (OUT-)
unnamed: J25.4, U34.5 (OUT+)
unnamed: J26.1, U35.5 (OUT+)
unnamed: J26.2, U35.8 (OUT-)
unnamed: J26.3, U36.8 (OUT-)
unnamed: J26.4, U36.5 (OUT+)
unnamed: J27.1, U37.5 (OUT+)
unnamed: J27.2, U37.8 (OUT-)
unnamed: J27.3, U38.8 (OUT-)
unnamed: J27.4, U38.5 (OUT+)
unnamed: J28.1, U39.5 (OUT+)
unnamed: J28.2, U39.8 (OUT-)
unnamed: J28.3, U40.8 (OUT-)
unnamed: J28.4, U40.5 (OUT+)
unnamed: J29.1, U41.5 (OUT+)
unnamed: J29.2, U41.8 (OUT-)
unnamed: J29.3, U42.8 (OUT-)
unnamed: J29.4, U42.5 (OUT+)
unnamed: J30.1, U43.5 (OUT+)
unnamed: J30.2, U43.8 (OUT-)
unnamed: J30.3, U44.8 (OUT-)
unnamed: J30.4, U44.5 (OUT+)
unnamed: J33.4, R2.1, R18.1
unnamed: JP1.1 (A), R17.1, U7.23 (GPIO9)
unnamed: RN2.8 (R1.2), U2.6 (LRCK)
unnamed: RN2.7 (R2.2), U2.7 (BCK)
unnamed: RN2.6 (R3.2), U2.8 (DIN1)
unnamed: RN2.5 (R4.2), U2.14 (SCKI)
unnamed: RN3.8 (R1.2), U3.6 (LRCK)
unnamed: RN3.7 (R2.2), U3.7 (BCK)
unnamed: RN3.6 (R3.2), U3.8 (DIN1)
unnamed: RN3.5 (R4.2), U3.14 (SCKI)
unnamed: RN4.8 (R1.2), U4.6 (LRCK)
unnamed: RN4.7 (R2.2), U4.7 (BCK)
unnamed: RN4.6 (R3.2), U4.8 (DIN1)
unnamed: RN4.5 (R4.2), U4.14 (SCKI)
unnamed: RN5.8 (R1.2), U8.6 (LRCK)
unnamed: RN5.7 (R2.2), U8.7 (BCK)
unnamed: RN5.6 (R3.2), U8.8 (DIN1)
unnamed: RN5.5 (R4.2), U8.14 (SCKI)
unnamed: C5.1, U1.1 (VINL)
unnamed: C3.1, U1.2 (VINR)
unnamed: C2.2, U1.3 (VREF1)
unnamed: C1.2, R3.1, U1.4 (VREF2)
unnamed: R7.1, U2.24 (MODE)
unnamed: C11.1, U2.26 (VCOM)
unnamed: R11.1, U3.24 (MODE)
unnamed: C14.1, U3.26 (VCOM)
unnamed: R15.1, U4.24 (MODE)
unnamed: C17.1, U4.26 (VCOM)
unnamed: TP3.1, U5.67 (PA8)
unnamed: TP4.1, U5.68 (PA9)
unnamed: C32.1, U5.8 (PC14), Y1.2
unnamed: C33.1, U5.9 (PC15), Y1.1
unnamed: TP1.1, U5.43 (PE13)
unnamed: TP2.1, U5.44 (PE14)
unnamed: C40.1, R32.1, U7.8 (EN/CHIP_PU)
unnamed: R33.1, U7.22 (GPIO8)
unnamed: R41.1, U8.24 (MODE)
unnamed: C45.1, U8.26 (VCOM)
unnamed: C71.1, U13.3 (IN+)
unnamed: C72.2, U13.4 (IN-)
unnamed: C73.1, U14.3 (IN+)
unnamed: C74.2, U14.4 (IN-)
unnamed: C75.1, U15.3 (IN+)
unnamed: C76.2, U15.4 (IN-)
unnamed: C79.1, U16.3 (IN+)
unnamed: C80.2, U16.4 (IN-)
unnamed: C83.1, U17.3 (IN+)
unnamed: C84.2, U17.4 (IN-)
unnamed: C85.1, U18.3 (IN+)
unnamed: C86.2, U18.4 (IN-)
unnamed: C89.1, U19.3 (IN+)
unnamed: C90.2, U19.4 (IN-)
unnamed: C91.1, U20.3 (IN+)
unnamed: C92.2, U20.4 (IN-)
unnamed: C95.1, U21.3 (IN+)
unnamed: C96.2, U21.4 (IN-)
unnamed: C97.1, U22.3 (IN+)
unnamed: C98.2, U22.4 (IN-)
unnamed: C101.1, U23.3 (IN+)
unnamed: C102.2, U23.4 (IN-)
unnamed: C103.1, U24.3 (IN+)
unnamed: C104.2, U24.4 (IN-)
unnamed: C107.1, U25.3 (IN+)
unnamed: C108.2, U25.4 (IN-)
unnamed: C109.1, U26.3 (IN+)
unnamed: C110.2, U26.4 (IN-)
unnamed: C113.1, U27.3 (IN+)
unnamed: C114.2, U27.4 (IN-)
unnamed: C115.1, U28.3 (IN+)
unnamed: C116.2, U28.4 (IN-)
unnamed: C119.1, U29.3 (IN+)
unnamed: C120.2, U29.4 (IN-)
unnamed: C121.1, U30.3 (IN+)
unnamed: C122.2, U30.4 (IN-)
unnamed: C125.1, U31.3 (IN+)
unnamed: C126.2, U31.4 (IN-)
unnamed: C127.1, U32.3 (IN+)
unnamed: C128.2, U32.4 (IN-)
unnamed: C131.1, U33.3 (IN+)
unnamed: C132.2, U33.4 (IN-)
unnamed: C133.1, U34.3 (IN+)
unnamed: C134.2, U34.4 (IN-)
unnamed: C137.1, U35.3 (IN+)
unnamed: C138.2, U35.4 (IN-)
unnamed: C139.1, U36.3 (IN+)
unnamed: C140.2, U36.4 (IN-)
unnamed: C143.1, U37.3 (IN+)
unnamed: C144.2, U37.4 (IN-)
unnamed: C145.1, U38.3 (IN+)
unnamed: C146.2, U38.4 (IN-)
unnamed: C149.1, U39.3 (IN+)
unnamed: C150.2, U39.4 (IN-)
unnamed: C151.1, U40.3 (IN+)
unnamed: C152.2, U40.4 (IN-)
unnamed: C155.1, U41.3 (IN+)
unnamed: C156.2, U41.4 (IN-)
unnamed: C157.1, U42.3 (IN+)
unnamed: C158.2, U42.4 (IN-)
unnamed: C161.1, U43.3 (IN+)
unnamed: C162.2, U43.4 (IN-)
unnamed: C163.1, U44.3 (IN+)
unnamed: C164.2, U44.4 (IN-)
PA11: U5.70 (PA11), U11.4 (I/O2)
PA12: U5.71 (PA12), U11.6 (I/O1)
PC13: C68.2, K1.1, R20.1, U5.7 (PC13)
SAI1_MCLK: RN2.4 (R4.1), RN3.4 (R4.1), RN4.4 (R4.1), RN5.4 (R4.1), U1.15 (SCKI), U5.1 (PE2)
USB1_DN: R42.1, U11.3 (I/O2)
USB1_DP: R43.1, U11.1 (I/O1)
USB2_DN: R45.2, U12.3 (I/O2)
USB2_DP: R44.2, U12.1 (I/O1)
VBAT_pin: D2.2, J13.1
VDD: C77.1, C78.2, C81.1, C82.2, C87.1, C88.2, C93.1, C94.2, C99.1, C100.2, C105.1, C106.2, C111.1, C112.2, C117.1, C118.2, C123.1, C124.2, C129.1, C130.2, C135.1, C136.2, C141.1, C142.2, C147.1, C148.2, C153.1, C154.2, C159.1, C160.2, C165.1, C166.2, J34.1, U13.6 (VDD), U14.6 (VDD), U15.6 (VDD), U16.6 (VDD), U17.6 (VDD), U18.6 (VDD), U19.6 (VDD), U20.6 (VDD), U21.6 (VDD), U22.6 (VDD), U23.6 (VDD), U24.6 (VDD), U25.6 (VDD), U26.6 (VDD), U27.6 (VDD), U28.6 (VDD), U29.6 (VDD), U30.6 (VDD), U31.6 (VDD), U32.6 (VDD), U33.6 (VDD), U34.6 (VDD), U35.6 (VDD), U36.6 (VDD), U37.6 (VDD), U38.6 (VDD), U39.6 (VDD), U40.6 (VDD), U41.6 (VDD), U42.6 (VDD), U43.6 (VDD), U44.6 (VDD)
